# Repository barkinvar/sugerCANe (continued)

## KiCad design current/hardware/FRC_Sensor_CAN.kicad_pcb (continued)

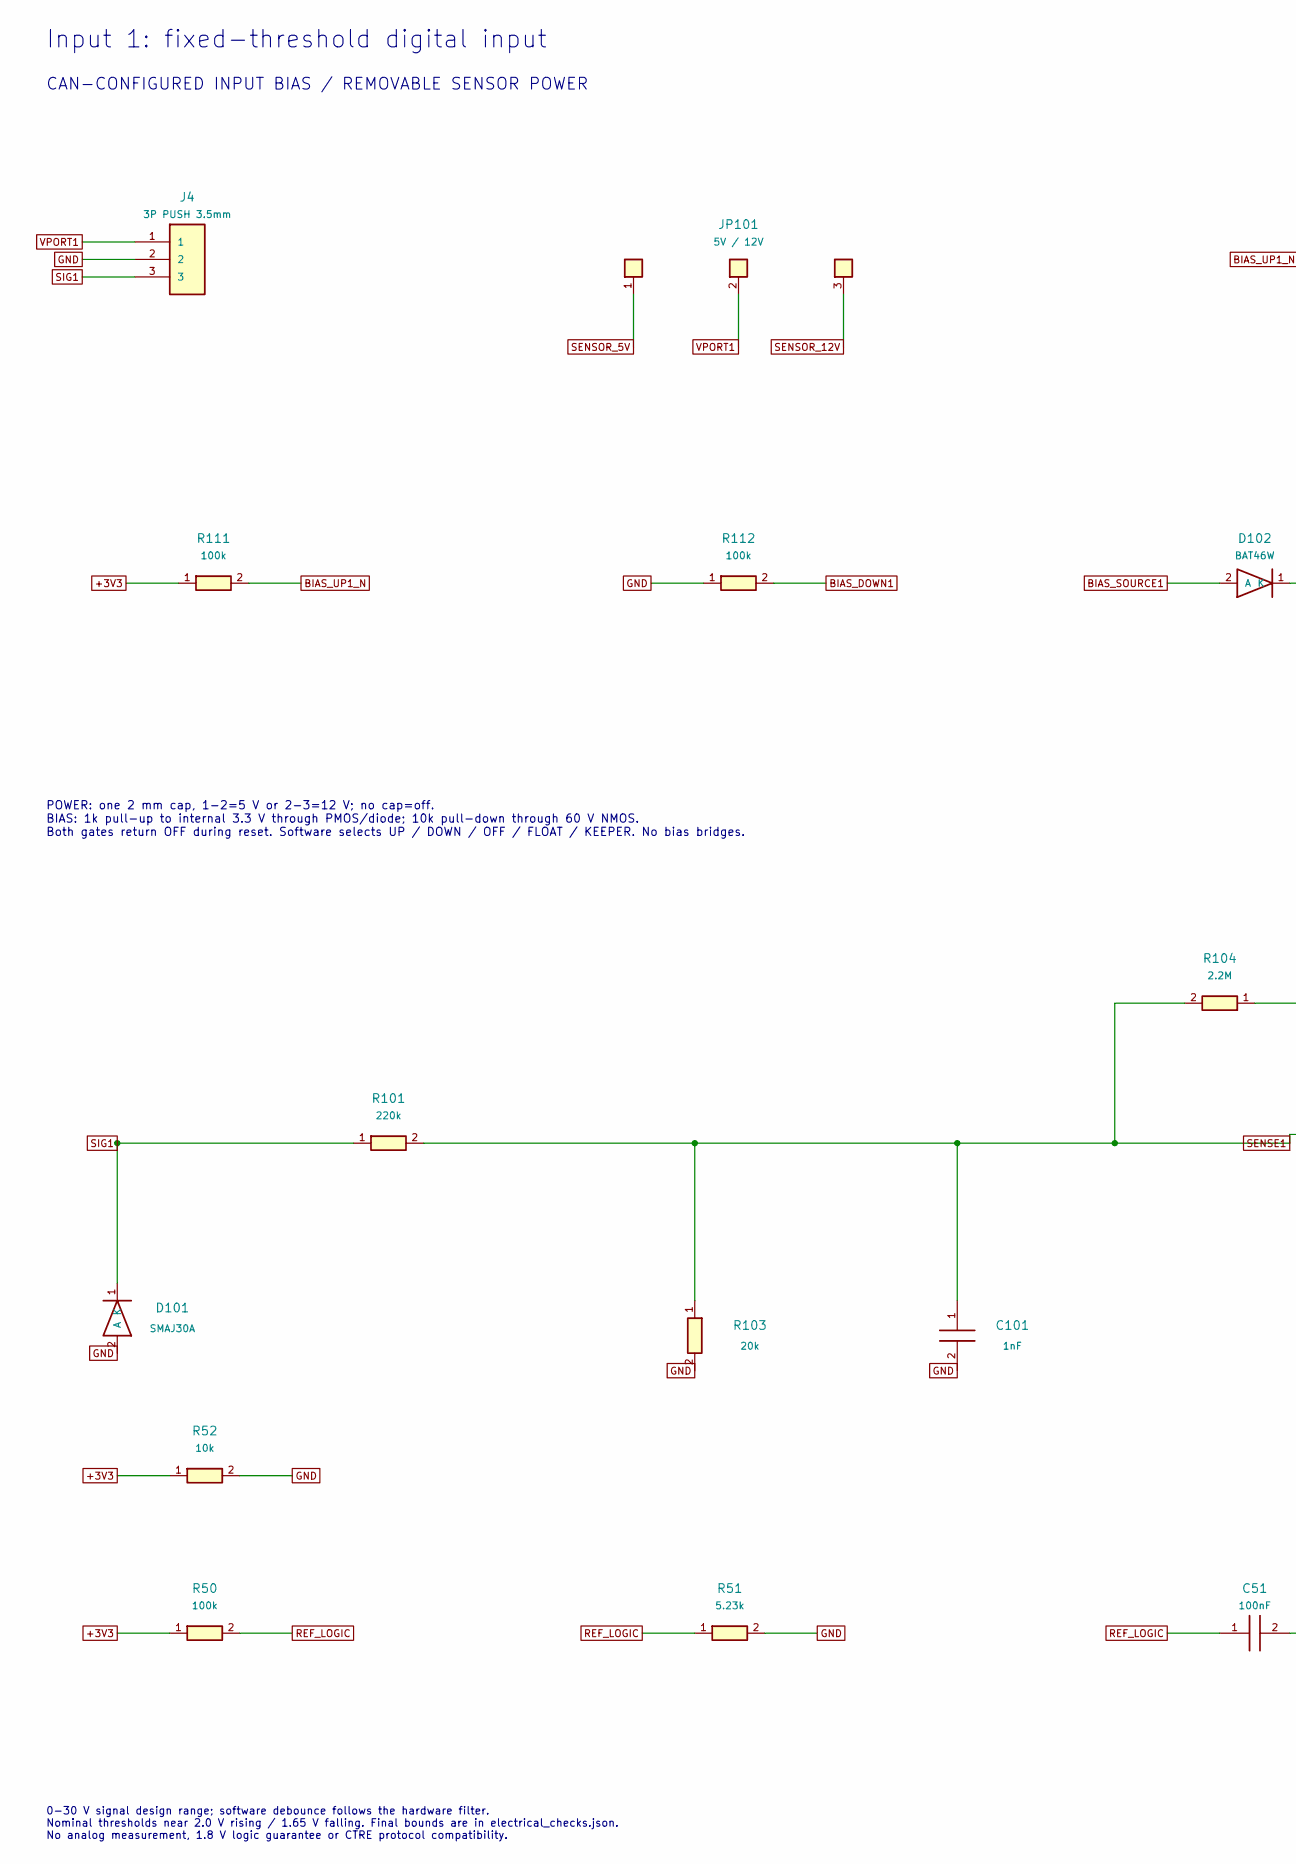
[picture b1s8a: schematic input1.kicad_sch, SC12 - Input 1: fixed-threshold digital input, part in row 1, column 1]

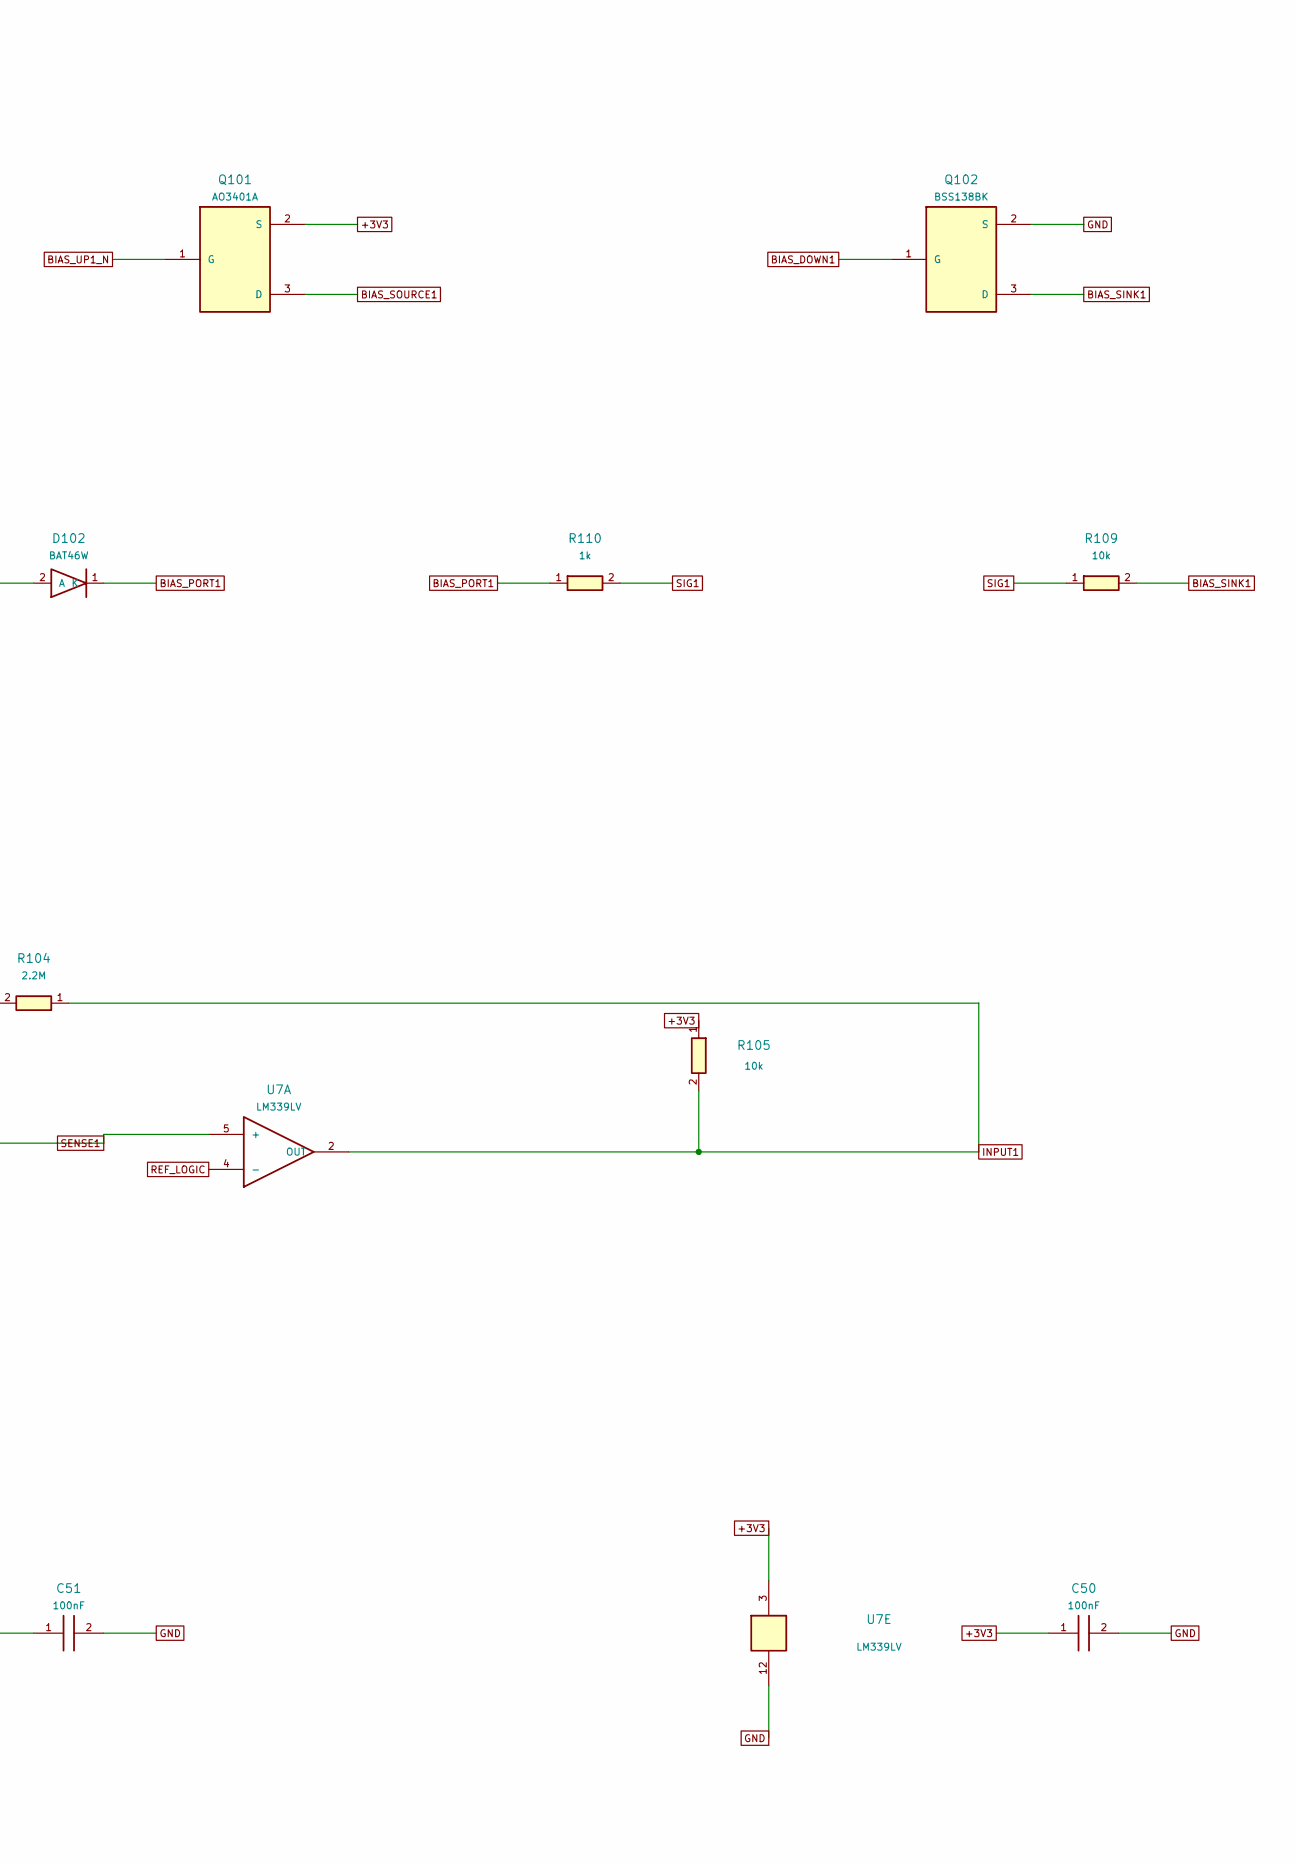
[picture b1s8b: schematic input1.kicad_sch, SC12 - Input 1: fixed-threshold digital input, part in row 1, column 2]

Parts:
C50, C51: 100nF; C_0805_2012Metric; MPN CL21B104KCFNNNE
C101: 1nF; C_0805_2012Metric; MPN CC0805JRNPO9BN102
D101: SMAJ30A; D_SMA; MPN SMAJ30A
D102: BAT46W; D_SOD-123; MPN BAT46W-E3-18
J4: 3P PUSH 3.5mm; Weidmuller_LSF_90_3P; MPN 1824430000
JP101: 5V / 12V; PinHeader_1x03_P2.00mm_Vertical; MPN M22-2010305
Q101: AO3401A; SOT-23; MPN AO3401A
Q102: BSS138BK; SOT-23; MPN BSS138BK,215
R50, R111, R112: 100k; R_0805_2012Metric; MPN 0805W8F1003T5E
R51: 5.23k; R_0805_2012Metric; MPN 0805W8F5231T5E
R52, R105: 10k; R_0805_2012Metric; MPN 0805W8F1002T5E
R101: 220k; R_0805_2012Metric; MPN 0805W8F2203T5E
R103: 20k; R_0805_2012Metric; MPN RC0805FR-0720KL
R104: 2.2M; R_0805_2012Metric; MPN RC0805FR-072M2L
R109: 10k; R_1206_3216Metric; MPN RC1206FR-0710KL
R110: 1k; R_0805_2012Metric; MPN 0805W8F1001T5E
U7: LM339LV; SOIC-14_3.9x8.7mm_P1.27mm; MPN LM339LVDR

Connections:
+3V3: C50.1, Q101.2 (S), R50.1, R52.1, R105.1, R111.1, U7.3; also elsewhere on the board
BIAS_DOWN1: Q102.1 (G), R112.2; also elsewhere on the board
BIAS_PORT1: D102.1 (K), R110.1
BIAS_SINK1: Q102.3 (D), R109.2
BIAS_SOURCE1: D102.2 (A), Q101.3 (D)
BIAS_UP1_N: Q101.1 (G), R111.2; also elsewhere on the board
GND: C50.2, C51.2, C101.2, D101.2 (A), J4.2, Q102.2 (S), R51.2, R52.2, R103.2, R112.1, U7.12; also elsewhere on the board
INPUT1: R104.1, R105.2, U7.2 (OUT); also elsewhere on the board
REF_LOGIC: C51.1, R50.2, R51.1, U7.4 (-); also elsewhere on the board
SENSE1: C101.1, R101.2, R103.1, R104.2, U7.5 (+)
SENSOR_5V: JP101.1; also elsewhere on the board
SENSOR_12V: JP101.3; also elsewhere on the board
SIG1: D101.1 (K), J4.3, R101.1, R109.1, R110.2
VPORT1: J4.1, JP101.2

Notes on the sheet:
Input 1: fixed-threshold digital input
CAN-CONFIGURED INPUT BIAS / REMOVABLE SENSOR POWER
POWER: one 2 mm cap, 1-2=5 V or 2-3=12 V; no cap=off. BIAS: 1k pull-up to internal 3.3 V through PMOS/diode; 10k pull-down through 60 V NMOS. Both gates return OFF during reset. Software selects UP / DOWN / OFF / FLOAT / KEEPER. No bias bridges.
0-30 V signal design range; software debounce follows the hardware filter. Nominal thresholds near 2.0 V rising / 1.65 V falling. Final bounds are in electrical_checks.json. No analog measurement, 1.8 V logic guarantee or CTRE protocol compatibility.

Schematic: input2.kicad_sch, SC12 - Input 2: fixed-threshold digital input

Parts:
C201: 1nF; C_0805_2012Metric; MPN CC0805JRNPO9BN102
D201: SMAJ30A; D_SMA; MPN SMAJ30A
D202: BAT46W; D_SOD-123; MPN BAT46W-E3-18
J5: 3P PUSH 3.5mm; Weidmuller_LSF_90_3P; MPN 1824430000
JP201: 5V / 12V; PinHeader_1x03_P2.00mm_Vertical; MPN M22-2010305
Q201: AO3401A; SOT-23; MPN AO3401A
Q202: BSS138BK; SOT-23; MPN BSS138BK,215
R201: 220k; R_0805_2012Metric; MPN 0805W8F2203T5E
R203: 20k; R_0805_2012Metric; MPN RC0805FR-0720KL
R204: 2.2M; R_0805_2012Metric; MPN RC0805FR-072M2L
R205: 10k; R_0805_2012Metric; MPN 0805W8F1002T5E
R209: 10k; R_1206_3216Metric; MPN RC1206FR-0710KL
R210: 1k; R_0805_2012Metric; MPN 0805W8F1001T5E
R211, R212: 100k; R_0805_2012Metric; MPN 0805W8F1003T5E
U7: LM339LV; SOIC-14_3.9x8.7mm_P1.27mm; MPN LM339LVDR

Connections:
+3V3: Q201.2 (S), R205.1, R211.1; also elsewhere on the board
BIAS_DOWN2: Q202.1 (G), R212.2; also elsewhere on the board
BIAS_PORT2: D202.1 (K), R210.1
BIAS_SINK2: Q202.3 (D), R209.2
BIAS_SOURCE2: D202.2 (A), Q201.3 (D)
BIAS_UP2_N: Q201.1 (G), R211.2; also elsewhere on the board
GND: C201.2, D201.2 (A), J5.2, Q202.2 (S), R203.2, R212.1; also elsewhere on the board
INPUT2: R204.1, R205.2, U7.1 (OUT); also elsewhere on the board
REF_LOGIC: U7.6 (-); also elsewhere on the board
SENSE2: C201.1, R201.2, R203.1, R204.2, U7.7 (+)
SENSOR_5V: JP201.1; also elsewhere on the board
SENSOR_12V: JP201.3; also elsewhere on the board
SIG2: D201.1 (K), J5.3, R201.1, R209.1, R210.2
VPORT2: J5.1, JP201.2

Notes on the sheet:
Input 2: fixed-threshold digital input
CAN-CONFIGURED INPUT BIAS / REMOVABLE SENSOR POWER
POWER: one 2 mm cap, 1-2=5 V or 2-3=12 V; no cap=off. BIAS: 1k pull-up to internal 3.3 V through PMOS/diode; 10k pull-down through 60 V NMOS. Both gates return OFF during reset. Software selects UP / DOWN / OFF / FLOAT / KEEPER. No bias bridges.
The reference divider/filter and comparator power connections are on input1. One fixed logic-compatible threshold for all three channels; no industrial threshold selector.
0-30 V signal design range; software debounce follows the hardware filter. Nominal thresholds near 2.0 V rising / 1.65 V falling. Final bounds are in electrical_checks.json. No analog measurement, 1.8 V logic guarantee or CTRE protocol compatibility.

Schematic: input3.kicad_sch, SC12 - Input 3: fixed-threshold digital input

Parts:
C301: 1nF; C_0805_2012Metric; MPN CC0805JRNPO9BN102
D301: SMAJ30A; D_SMA; MPN SMAJ30A
D302: BAT46W; D_SOD-123; MPN BAT46W-E3-18
J6: 3P PUSH 3.5mm; Weidmuller_LSF_90_3P; MPN 1824430000
JP301: 5V / 12V; PinHeader_1x03_P2.00mm_Vertical; MPN M22-2010305
Q301: AO3401A; SOT-23; MPN AO3401A
Q302: BSS138BK; SOT-23; MPN BSS138BK,215
R301: 220k; R_0805_2012Metric; MPN 0805W8F2203T5E
R303: 20k; R_0805_2012Metric; MPN RC0805FR-0720KL
R304: 2.2M; R_0805_2012Metric; MPN RC0805FR-072M2L
R305: 10k; R_0805_2012Metric; MPN 0805W8F1002T5E
R309: 10k; R_1206_3216Metric; MPN RC1206FR-0710KL
R310: 1k; R_0805_2012Metric; MPN 0805W8F1001T5E
R311, R312: 100k; R_0805_2012Metric; MPN 0805W8F1003T5E
U7: LM339LV; SOIC-14_3.9x8.7mm_P1.27mm; MPN LM339LVDR

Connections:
+3V3: Q301.2 (S), R305.1, R311.1; also elsewhere on the board
BIAS_DOWN3: Q302.1 (G), R312.2; also elsewhere on the board
BIAS_PORT3: D302.1 (K), R310.1
BIAS_SINK3: Q302.3 (D), R309.2
BIAS_SOURCE3: D302.2 (A), Q301.3 (D)
BIAS_UP3_N: Q301.1 (G), R311.2; also elsewhere on the board
GND: C301.2, D301.2 (A), J6.2, Q302.2 (S), R303.2, R312.1; also elsewhere on the board
INPUT3: R304.1, R305.2, U7.14 (OUT); also elsewhere on the board
REF_LOGIC: U7.8 (-); also elsewhere on the board
SENSE3: C301.1, R301.2, R303.1, R304.2, U7.9 (+)
SENSOR_5V: JP301.1; also elsewhere on the board
SENSOR_12V: JP301.3; also elsewhere on the board
SIG3: D301.1 (K), J6.3, R301.1, R309.1, R310.2
VPORT3: J6.1, JP301.2

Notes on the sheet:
Input 3: fixed-threshold digital input
CAN-CONFIGURED INPUT BIAS / REMOVABLE SENSOR POWER
POWER: one 2 mm cap, 1-2=5 V or 2-3=12 V; no cap=off. BIAS: 1k pull-up to internal 3.3 V through PMOS/diode; 10k pull-down through 60 V NMOS. Both gates return OFF during reset. Software selects UP / DOWN / OFF / FLOAT / KEEPER. No bias bridges.
The reference divider/filter and comparator power connections are on input1. One fixed logic-compatible threshold for all three channels; no industrial threshold selector.
0-30 V signal design range; software debounce follows the hardware filter. Nominal thresholds near 2.0 V rising / 1.65 V falling. Final bounds are in electrical_checks.json. No analog measurement, 1.8 V logic guarantee or CTRE protocol compatibility.

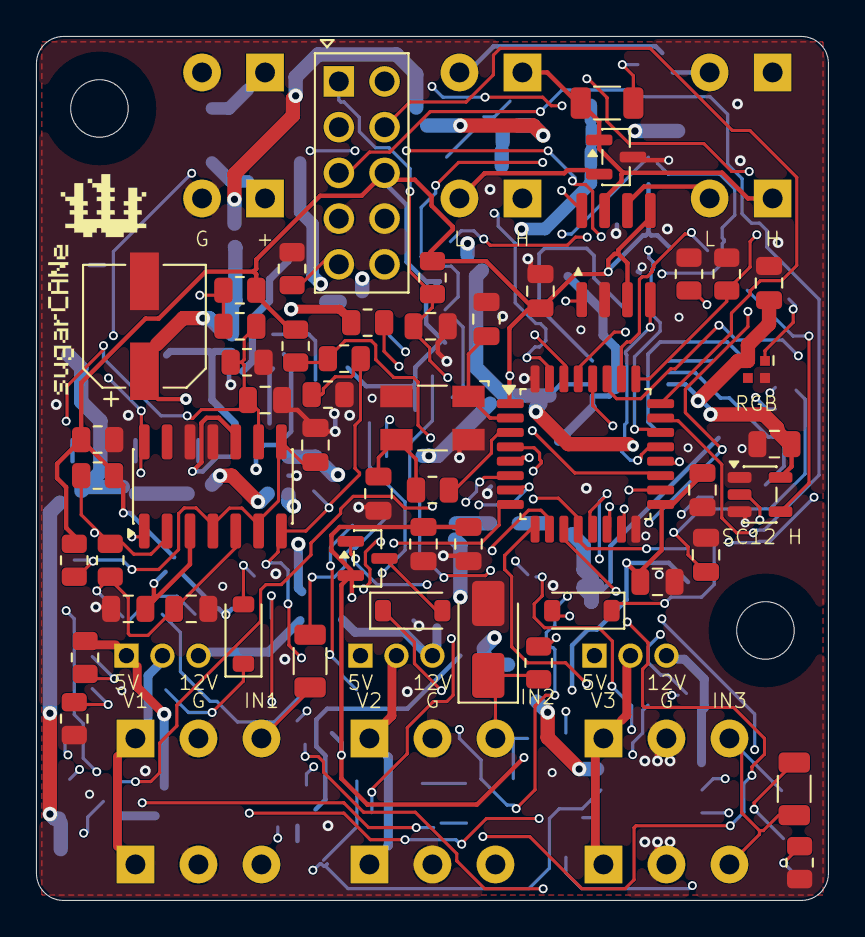
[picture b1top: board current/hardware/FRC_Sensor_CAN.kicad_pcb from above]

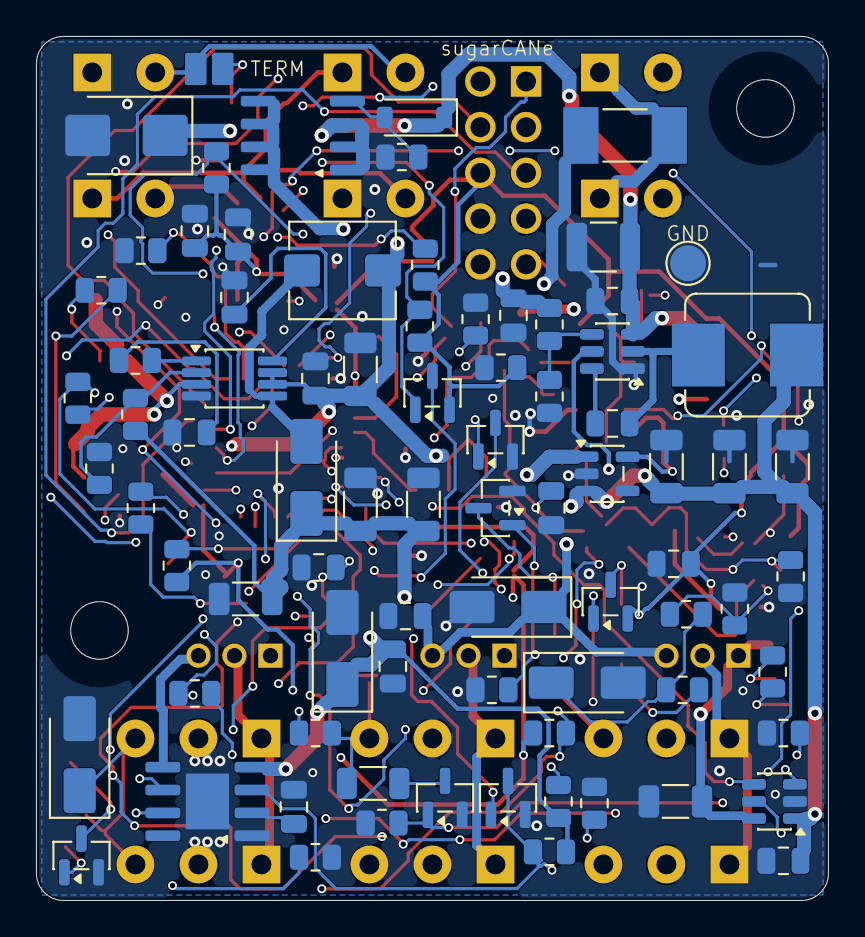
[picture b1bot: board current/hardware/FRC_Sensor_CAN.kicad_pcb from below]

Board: 4 copper layers, 44.0 x 48.0 mm, 144 parts (81 on the bottom side), 77 nets.

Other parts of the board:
H1, H2: M3 NPTH

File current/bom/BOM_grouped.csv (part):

MPN,Manufacturer,Quantity,References,Value,Footprint,Voltage,Tolerance,Power_W,Dielectric,Assembly,Supplier,Supplier_part,LCSC_part,MOQ,Multiple,Unit_USD_first_tier,Extended_USD_first_tier,Observed_stock,Checked_date,Supplier_URL,DigiKey_SKU,Factory_stock_status,Component_notes
0451003.MRL,Littelfuse,1,F1,3A FAST,FRC_Sensor_CAN:Fuse_Littelfuse-NANO2-451_453,,,,,Factory SMT,JLCPCB,C13982,C13982,1,1,0.2556,0.2556,45148,2026-09-10,https://jlcpcb.com/partdetail/C13982,F2583CT-ND,Public JLC stock sufficient for 10 boards plus allowance; not reserved,Secondary 3 A fast fuse. Feed only from a protected FRC distribution branch; board fuse does not replace the branch fuse.
0805W8F1001T5E,UNI-ROYAL,4,"R4, R110, R210, R310",1k,FRC_Sensor_CAN:R_0805_2012Metric,,1%,0.125,,Factory SMT,JLCPCB,C17513,C17513,1,1,0.0042,0.0168,29728751,2026-09-10,https://jlcpcb.com/partdetail/C17513,,Public JLC stock sufficient for 10 boards plus allowance; not reserved,3V3 bleed retained for conservative powered-off leakage budget; 3.3 mA load.
0805W8F1002T5E,UNI-ROYAL,12,"R3, R21, R22, R40, R41, R105, R205, R305, R52, R71, R75, R31",10k,FRC_Sensor_CAN:R_0805_2012Metric,,1%,0.125,,Factory SMT,JLCPCB,C17414,C17414,1,1,0.0039,0.0468,52860584,2026-09-10,https://jlcpcb.com/partdetail/C17414,,Public JLC stock sufficient for 10 boards plus allowance; not reserved,Gate pull-down; maximum 1 mA nominal zener current at 22 V input.
0805W8F1003T5E,UNI-ROYAL,8,"R50, R111, R112, R211, R212, R311, R312, R70",100k,FRC_Sensor_CAN:R_0805_2012Metric,,1%,0.125,,Factory SMT,JLCPCB,C149504,C149504,1,1,0.0059,0.0472,4745764,2026-09-10,https://jlcpcb.com/partdetail/C149504,,Public JLC stock sufficient for 10 boards plus allowance; not reserved,
0805W8F1152T5E,UNI-ROYAL,1,R61,11.5k,FRC_Sensor_CAN:R_0805_2012Metric,,1%,0.125,,Factory SMT,JLCPCB,C17418,C17418,1,1,0.0041,0.0041,3238,2026-09-10,https://jlcpcb.com/partdetail/C17418,,Public JLC stock sufficient for 10 boards plus allowance; not reserved,"Feedback lower arm, 1%. 12.003V nominal with 1.238V reference."
0805W8F2203T5E,UNI-ROYAL,3,"R101, R201, R301",220k,FRC_Sensor_CAN:R_0805_2012Metric,,1%,0.125,,Factory SMT,JLCPCB,C17556,C17556,1,1,0.005,0.015,289378,2026-09-10,https://jlcpcb.com/partdetail/C17556,,Public JLC stock sufficient for 10 boards plus allowance; not reserved,One series resistor; loses Rev B single-resistor-short tolerance. 150 V working rating; input 0-30 V target.
0805W8F3300T5E,UNI-ROYAL,1,R30,330,FRC_Sensor_CAN:R_0805_2012Metric,,1%,0.125,,Factory SMT,JLCPCB,C17630,C17630,1,1,0.0054,0.0054,2316763,2026-09-10,https://jlcpcb.com/partdetail/C17630,,Public JLC stock sufficient for 10 boards plus allowance; not reserved,330 ohm LED data series resistor; short local route after level buffer.
0805W8F5231T5E,UNI-ROYAL,1,R51,5.23k,FRC_Sensor_CAN:R_0805_2012Metric,,1%,0.125,,Factory SMT,JLCPCB,C17739,C17739,1,1,0.0023,0.0023,2225,2026-09-10,https://jlcpcb.com/partdetail/C17739,,Public JLC stock sufficient for 10 boards plus allowance; not reserved,
0805W8F5902T5E,UNI-ROYAL,1,R10,59k,FRC_Sensor_CAN:R_0805_2012Metric,,1%,0.125,,Factory SMT,JLCPCB,C17763,C17763,1,1,0.0023,0.0023,6289,2026-09-10,https://jlcpcb.com/partdetail/C17763,,Public JLC stock sufficient for 10 boards plus allowance; not reserved,
1206W4F1200T5E,UNI-ROYAL,1,R42,120,FRC_Sensor_CAN:R_1206_3216Metric,,1%,0.25,,Factory SMT,JLCPCB,C17909,C17909,1,1,0.0074,0.0074,706352,2026-09-10,https://jlcpcb.com/partdetail/C17909,,Public JLC stock sufficient for 10 boards plus allowance; not reserved,Use termination only if board is the physical end of the CAN trunk.
1824420000,Weidmuller,3,"J1, J2, J3",2P PUSH 3.5mm,FRC_Sensor_CAN:Weidmuller_LSF_90_2P,,,,,Hand solder,DigiKey,281-2020-ND,,1,1,1.63,4.89,12775,2026-09-10,https://www.digikey.com/en/products/detail/weidm%C3%BCller/1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,281-2020-ND,External procurement candidate; JLCPCB stock not confirmed,"Horizontal /90 push-in; 8 mm strip, 7 mm pin-row spacing, two solder pins per pole."
1824430000,Weidmuller,3,"J4, J5, J6",3P PUSH 3.5mm,FRC_Sensor_CAN:Weidmuller_LSF_90_3P,,,,,Hand solder,DigiKey,281-2021-ND,,1,1,2.21,6.63,1698,2026-09-10,https://www.digikey.com/en/products/detail/weidm%C3%BCller/1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,281-2021-ND,External procurement candidate; JLCPCB stock not confirmed,"Horizontal /90 push-in; 8 mm strip, 7 mm pin-row spacing, two solder pins per pole."
ABM3B-8.000MHZ-B2-T,Abracon,1,Y1,8MHz 18pF,FRC_Sensor_CAN:Abracon_ABM3B_5.0x3.2mm,,,,,Factory SMT,JLCPCB,C83312,C83312,1,1,0.5892,0.5892,6741,2026-09-10,https://jlcpcb.com/partdetail/C83312,535-9720-1-ND,Public JLC stock sufficient for 10 boards plus allowance; not reserved,Abracon recommended land pattern: 1.8x1.2mm pads on 4.0x2.4mm centers; pads 2/4 ground.
AO3401A,Alpha & Omega Semiconductor,3,"Q101, Q201, Q301",AO3401A,FRC_Sensor_CAN:SOT-23,,,,,Factory SMT,JLCPCB,C15127,C15127,1,1,0.0943,0.2829,519549,2026-09-10,https://jlcpcb.com/partdetail/C15127,,Public JLC stock sufficient for 10 boards plus allowance; not reserved,"3.3 V bias source, active-low gate. BAT46W isolates positive field voltage."
AO4485,Alpha & Omega Semiconductor,1,Q1,AO4485,FRC_Sensor_CAN:SOIC-8_3.9x4.9mm_P1.27mm,,,,,Factory SMT,JLCPCB,C51499,C51499,1,1,0.2951,0.2951,72841,2026-09-10,https://jlcpcb.com/partdetail/C51499,785-1551-1-ND,Public JLC stock sufficient for 10 boards plus allowance; not reserved,"Reverse-polarity PMOS: drain toward input, source toward load. Not a reverse-current blocker when on."
AP2112K-3.3TRG1,Diodes Incorporated,1,U2,AP2112K-3.3,FRC_Sensor_CAN:SOT-23-5,,,,,Factory SMT,JLCPCB,C51118,C51118,1,1,0.1712,0.1712,60472,2026-09-10,https://jlcpcb.com/partdetail/C51118,AP2112K-3.3TRG1DICT-ND,Public JLC stock sufficient for 10 boards plus allowance; not reserved,
B240A-13-F,Diodes Incorporated,2,"D4, D5",B240A,FRC_Sensor_CAN:D_SMA,,,,,Factory SMT,JLCPCB,C92506,C92506,1,1,0.0951,0.1902,163590,2026-09-10,https://jlcpcb.com/partdetail/C92506,,Public JLC stock sufficient for 10 boards plus allowance; not reserved,"2A 40V Schottky rectifier; cathode on BOOST_12V, before U9 output protection."
BAT46W-E3-18,Vishay,3,"D102, D202, D302",BAT46W,FRC_Sensor_CAN:D_SOD-123,,,,,Factory SMT,JLCPCB,C5557780,C5557780,1,1,0.1309,0.3927,4733,2026-09-10,https://jlcpcb.com/partdetail/C5557780,BAT46W-E3-18GICT-ND,Public JLC stock sufficient for 10 boards plus allowance; not reserved,
"BSS138BK,215",Nexperia,5,"Q102, Q202, Q302, Q2, Q3",BSS138BK,FRC_Sensor_CAN:SOT-23,,,,,Factory SMT,JLCPCB,C282529,C282529,1,1,0.0669,0.3345,70842,2026-09-10,https://jlcpcb.com/partdetail/C282529,,Public JLC stock sufficient for 10 boards plus allowance; not reserved,"60 V bias sink, active-high gate; 6.5 ohm max at VGS=2.5 V, 25 C."
CC0805JRNPO9BN102,YAGEO,3,"C101, C201, C301",1nF,FRC_Sensor_CAN:C_0805_2012Metric,50V,5%,,C0G,Factory SMT,JLCPCB,C62774,C62774,1,1,0.0137,0.0411,1141135,2026-09-10,https://jlcpcb.com/partdetail/C62774,,Public JLC stock sufficient for 10 boards plus allowance; not reserved,
CC0805JRNPO9BN200,YAGEO,2,"C25, C26",20pF,FRC_Sensor_CAN:C_0805_2012Metric,50V,5%,,C0G,Factory SMT,JLCPCB,C105173,C105173,1,1,0.0114,0.0228,534289,2026-09-10,https://jlcpcb.com/partdetail/C105173,,Public JLC stock sufficient for 10 boards plus allowance; not reserved,
CC0805KRX7R9BB333,YAGEO,1,C69,33nF,FRC_Sensor_CAN:C_0805_2012Metric,50V,10%,,X7R,Factory SMT,JLCPCB,C107150,C107150,1,1,0.012,0.012,1799721,2026-09-10,https://jlcpcb.com/partdetail/C107150,311-1374-1-ND,Public JLC stock sufficient for 10 boards plus allowance; not reserved,"13k/33nF Type-II compensation; low crossover analytical screen, physical loop qualification required."
CL21B103KBANNNC,Samsung Electro-Mechanics,2,"C72, C73",10nF,FRC_Sensor_CAN:C_0805_2012Metric,50V,5%,,X7R,Factory SMT,JLCPCB,C1710,C1710,1,1,0.013,0.026,2603295,2026-09-10,https://jlcpcb.com/partdetail/C1710,,Public JLC stock sufficient for 10 boards plus allowance; not reserved,ADC anti-noise filter. Use long ADC acquisition time; firmware also measures internal VREFINT.
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
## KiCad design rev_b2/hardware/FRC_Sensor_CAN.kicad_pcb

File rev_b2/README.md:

# FRC Sensor CAN — Rev B-2

**Scope: Rev B-2.** [Revision overview](https://github.com/barkinvar/candi-clone/blob/main/rev_b2/README.md) · [All revisions](https://github.com/barkinvar/candi-clone/blob/main/REVISIONS.md).

**China factory-assembly variant of the horizontal-connector Rev B.** Three sensor inputs, selectable regulated 5 V or battery sensor power, a 5–22 V board-input target and a 60 × 68 mm PCB. All 144 components mount on top. This is an unbuilt prototype with a complete quotation/build-data package; factory sourcing, panel engineering and placement review are still required.

The board uses horizontal **Weidmüller 1824420000** (power/CAN, two poles) and **1824430000** (sensors, three poles), LSF-SMT 3.50 **/90**. Reserve 60 × 76.1 mm for the assembly before cable space; the terminals are 8.5 mm high.

B-2 changes 37 resistors and 12 bypass capacitors to checked equivalents, and buys eight unchanged MPNs from cheaper observed sources. Nominal consumed component cost falls from $59.30 to **$46.35**, before MOQ, factory fees and shipping. No parts were deleted. The circuit, copper geometry, connector pinouts and firmware remain equivalent to Rev B.

## Order and cost

- [Factory upload packet](order/RevB2_Factory_Upload.zip)
- [Factory order instructions](docs/FACTORY_ORDER.md), [Gerber ZIP](order/RevB2_Gerbers.zip)
- [Complete turnkey BOM](bom/BOM_turnkey.csv), [JLCPCB matching BOM](bom/BOM_JLCPCB.csv), [factory CPL](output/assembly/CPL_JLCPCB.csv), [loose accessories](bom/ACCESSORIES.csv)
- [Estimated order costs](docs/COST.md), [cost spreadsheet](bom/cost_estimate.csv), [MOQ purchase quantities](bom/procurement_quantities.csv)
- [Exact part changes](docs/PART_CHANGES.md), [capacitor audit](docs/PASSIVE_REVIEW.md)

Budget roughly **$300–390 total for two assembled boards**, or **$435–535 for five**, including estimated shipping and excluding import taxes and optional factory programming. JLCPCB publishes a two-board minimum. These are engineering estimates, not a live quotation; the MCU and connectors require procurement review. This prototype is not yet a competitive retail-cost design.

## Engineering files

- [KiCad project](hardware/FRC_Sensor_CAN.kicad_pro), [schematic](hardware/FRC_Sensor_CAN.kicad_sch), [PCB](hardware/FRC_Sensor_CAN.kicad_pcb)
- [Assembly drawing](output/assembly/top_assembly.pdf), [schematic PDF](output/assembly/schematic.pdf), [interactive BOM](output/assembly/interactive_bom.html), [STEP](output/mechanical/FRC_Sensor_CAN.step)
- [Printable handbook](output/documentation/FRC_Sensor_CAN_RevB2_Handbook.pdf), [printable BOM](output/documentation/BOM_RevB2.pdf)
- [Wiring and configuration](docs/WIRING.md), [firmware/programming](firmware/README.md), [robot integration](examples/README.md), [validation](docs/VALIDATION.md), [qualification worksheet](docs/QUALIFICATION.md)

The input range is a design target measured at the board connector under load. VBAT follows the input and is not regulated 12 V. Shared sensor budgets are 300 mA on 5 V and 300 mA on VBAT, not per-port. A low battery can stop an industrial sensor with a 10 V minimum supply. Signal inputs accept positive 0–30 V through the protected divider with common ground; logic-mode targets are LOW ≤0.8 V / HIGH ≥2.4 V. The design does not promise 1.8 V logic or CTRE Phoenix/Tuner compatibility.

Native and exported-data checks are computational evidence. Actual thermal, surge, CAN, sensor and programmer tests remain pending. All shunts ship loose and all sensor-power selectors open. No physical board, purchase or factory upload has been made.

See [tools](TOOLS.md), [sources](docs/SOURCES_AND_LICENSES.md) and [factory requirements](docs/FACTORY_ORDER.md) before manufacturing.

## Additional board views

Connector housings use official manufacturer STEP geometry; see [connector verification](docs/CONNECTORS.md). Render colors are illustrative.

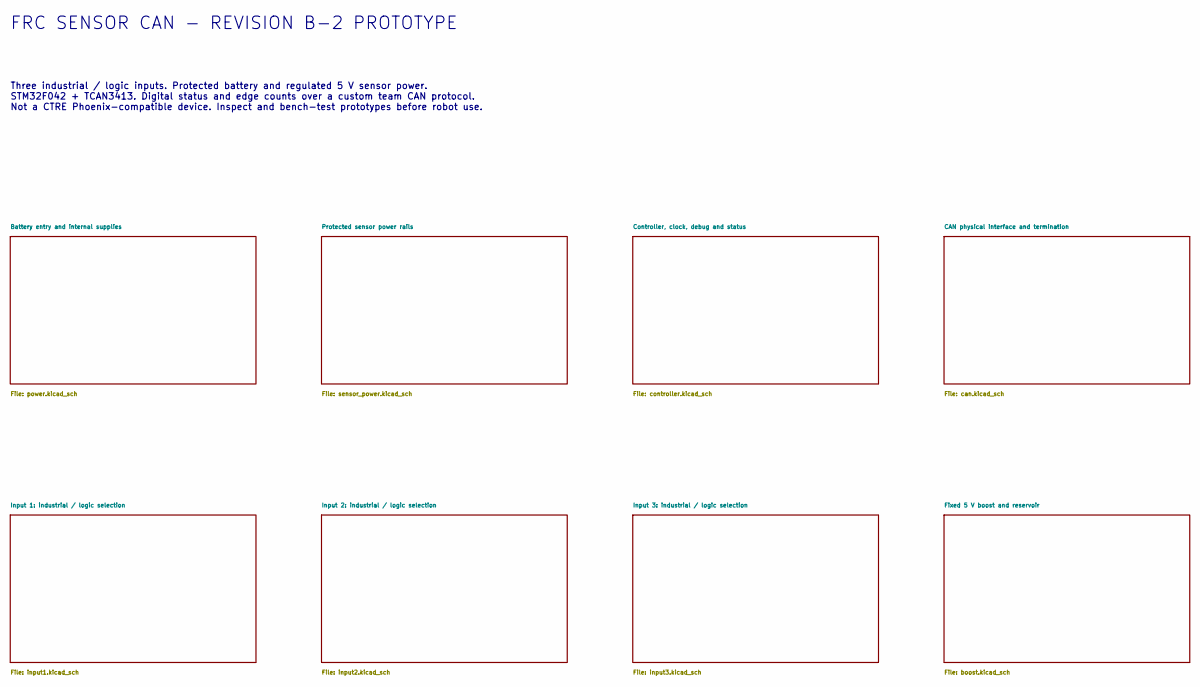
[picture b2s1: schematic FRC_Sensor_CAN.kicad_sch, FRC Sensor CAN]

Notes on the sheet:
FRC SENSOR CAN - REVISION B-2 PROTOTYPE
Three industrial / logic inputs. Protected battery and regulated 5 V sensor power. STM32F042 + TCAN3413. Digital status and edge counts over a custom team CAN protocol. Not a CTRE Phoenix-compatible device. Inspect and bench-test prototypes before robot use.
